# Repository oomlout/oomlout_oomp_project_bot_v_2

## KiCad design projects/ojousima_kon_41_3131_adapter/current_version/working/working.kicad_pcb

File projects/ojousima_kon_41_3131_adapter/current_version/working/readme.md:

# kon_41_3131
 
## summary 
* id: ojousima_kon_41_3131_adapter
* user: ojousima
* name: kon_41_3131
* board: adapter
* repo: https://github.com/ojousima/kon-41.3131
* src_file_repo_kicad_pcb: adapter_board/adapter.kicad_pcb
* src_file_repo_kicad_pcb_link: https://github.com/ojousima/kon-41.3131/tree/master/adapter_board/adapter.kicad_pcb

* src_file_repo_sch: adapter_board/adapter.sch
* src_file_repo_sch_link: https://github.com/ojousima/kon-41.3131/tree/master/adapter_board/adapter.sch
* full details link: https://github.com/oomlout/oomlout_oomp_project_bot_v_2/tree/main/projects/ojousima_kon_41_3131_adapter/current_version/working

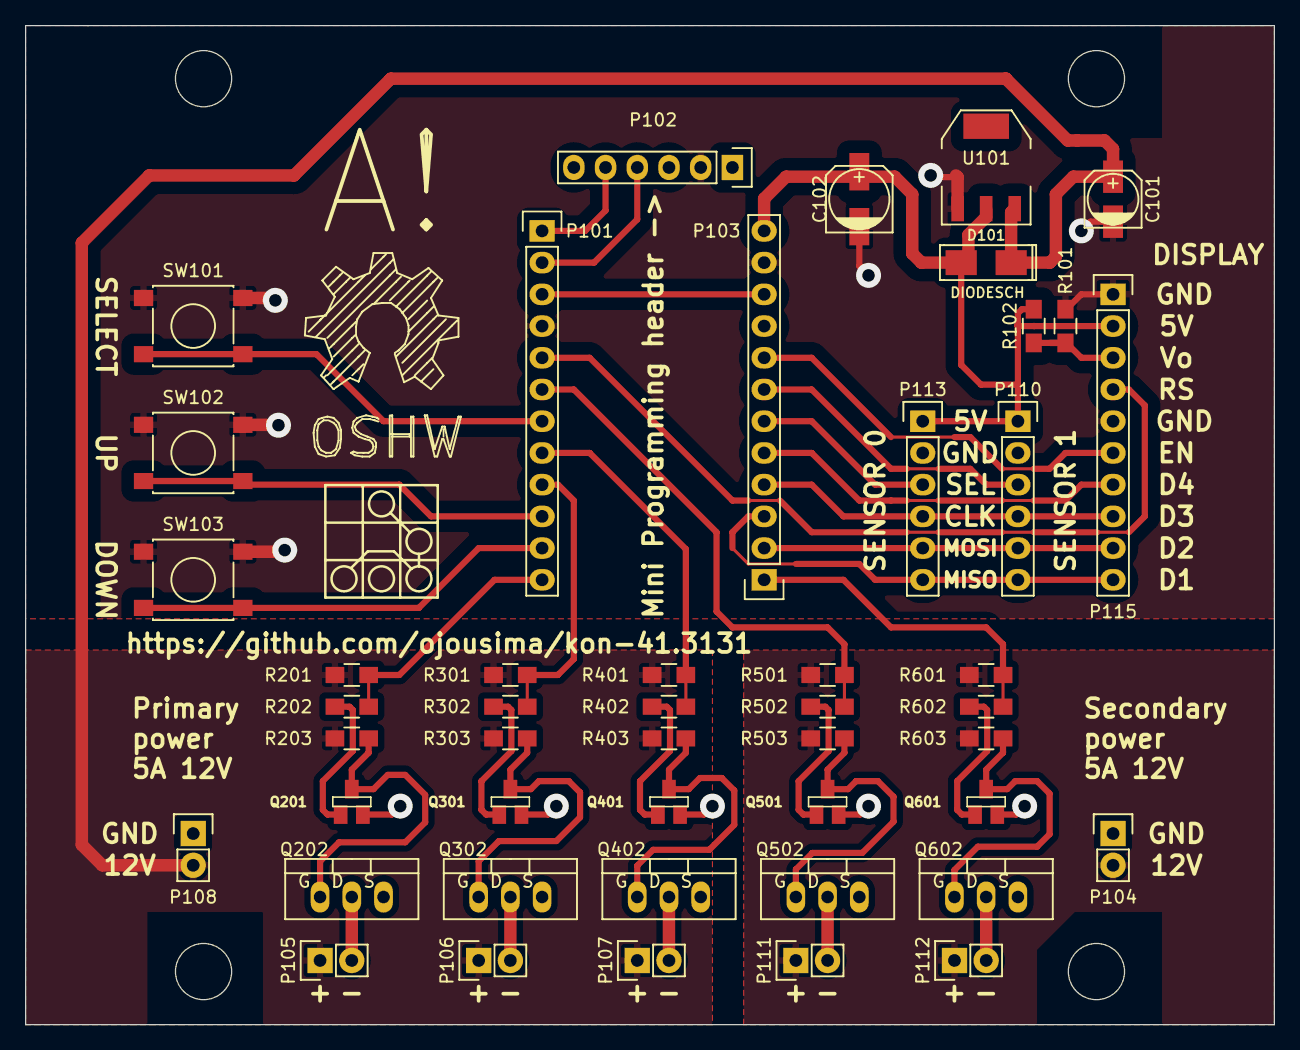
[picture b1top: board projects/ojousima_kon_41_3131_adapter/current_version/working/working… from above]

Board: 2 copper layers, 100.0 x 80.0 mm, 48 parts (0 on the bottom side), 39 nets.

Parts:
C101: 10u; c_elec_4x5.3
C102: 100u; c_elec_5x5.8
D101: DIODESCH; SMA_WAVE
LOGO101: OPEN_HARDWARE_2; Symbol_OSHW-Logo_SilkScreen_BIG
P101, P103: CONN_01X12; Pin_Header_Straight_1x12
P102, P110, P113: CONN_01X06; Pin_Header_Straight_1x06
P104, P105, P106, P107, P108, P111, P112: CONN_01X02; Pin_Header_Straight_1x02
P115: CONN_01X10; Pin_Header_Straight_1x10
Q201, Q301, Q401, Q501, Q601: BC850; SOT23EBC
Q202, Q302, Q402, Q502, Q602: IRF530N; TO-220_FET-GDS_Vertical
R101, R102: R; R_0805_HandSoldering
R201, R203, R301, R303, R401, R403, R501, R503, R601, R603: 10k; R_0805_HandSoldering
R202, R302, R402, R502, R602: 1k; R_0805_HandSoldering
SW101, SW102, SW103: SPST; SW_SPST_PTS645
U101: LD1117S50TR; SOT-223

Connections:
/5V: C102.1, D101.1, P103.12, P110.1, P113.1, P115.2, R101.1, U101.2
/BT0: P101.7, SW101.2
/BT1: P101.10, SW102.2
/BT2: P101.11, SW103.2
/D4: P103.5, P115.7
/MISO: P103.3, P110.6, P113.6, P115.10
/MOSI: P103.2, P110.5, P113.5, P115.9
/PWM0/12V: C101.1, D101.2, P105.1, P106.1, P107.1, P108.2, R201.1, R203.1, R301.1, R303.1, R401.1, R403.1, U101.3
/PWM0/Drain: P105.2, Q202.D
/PWM0/INV_PWM: P101.12, R201.2, R202.2
/PWM1/Drain: P106.2, Q302.D
/PWM1/INV_PWM: P101.9, R301.2, R302.2
/PWM2/Drain: P107.2, Q402.D
/PWM2/INV_PWM: P101.8, R401.2, R402.2
/PWM3/12V: P104.2, P111.1, P112.1, R501.1, R503.1, R601.1, R603.1
/PWM3/Drain: P111.2, Q502.D
/PWM3/INV_PWM: P101.6, R501.2, R502.2
/PWM4/Drain: P112.2, Q602.D
/PWM4/INV_PWM: P103.1, R601.2, R602.2
/RESET: P101.3, P103.10
/RS: P101.5, P115.4
/RXI: P101.2, P102.4
/SCLK: P103.4, P110.4, P113.4, P115.8
/SEL0: P103.6, P113.3
/SEL1: P103.7, P110.3
/SEL2: P103.8, P115.6
/TXO: P101.1, P102.5
/Vo: P115.3, R101.2, R102.1
GND: C101.2, C102.2, P101.4, P102.2, P103.11, P104.1, P108.1, P110.2, P113.2, P115.1, P115.5, Q201.1, Q202.S, Q301.1, Q302.S, Q401.1, Q402.S, Q501.1, Q502.S, Q601.1, Q602.S, R102.2, SW101.1, SW102.1, SW103.1, U101.1
unnamed: Q201.2, R202.1
unnamed: Q201.3, Q202.G, R203.2
unnamed: Q301.2, R302.1
unnamed: Q301.3, Q302.G, R303.2
unnamed: Q401.2, R402.1
unnamed: Q401.3, Q402.G, R403.2
unnamed: Q501.2, R502.1
unnamed: Q501.3, Q502.G, R503.2
unnamed: Q601.2, R602.1
unnamed: Q601.3, Q602.G, R603.2

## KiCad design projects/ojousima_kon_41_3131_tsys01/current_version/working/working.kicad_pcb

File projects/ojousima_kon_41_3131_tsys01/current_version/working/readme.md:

# kon_41_3131
 
## summary 
* id: ojousima_kon_41_3131_tsys01
* user: ojousima
* name: kon_41_3131
* board: tsys01
* repo: https://github.com/ojousima/kon-41.3131
* src_file_repo_kicad_pcb: TSYS01-shield/tsys01.kicad_pcb
* src_file_repo_kicad_pcb_link: https://github.com/ojousima/kon-41.3131/tree/master/TSYS01-shield/tsys01.kicad_pcb
* src_file_repo_kicad_sch: adapter_board/PWM.kicad_sch
* src_file_repo_kicad_sch_link: https://github.com/ojousima/kon-41.3131/tree/master/adapter_board/PWM.kicad_sch

* src_file_repo_sch: TSYS01-shield/tsys01.sch
* src_file_repo_sch_link: https://github.com/ojousima/kon-41.3131/tree/master/TSYS01-shield/tsys01.sch
* full details link: https://github.com/oomlout/oomlout_oomp_project_bot_v_2/tree/main/projects/ojousima_kon_41_3131_tsys01/current_version/working

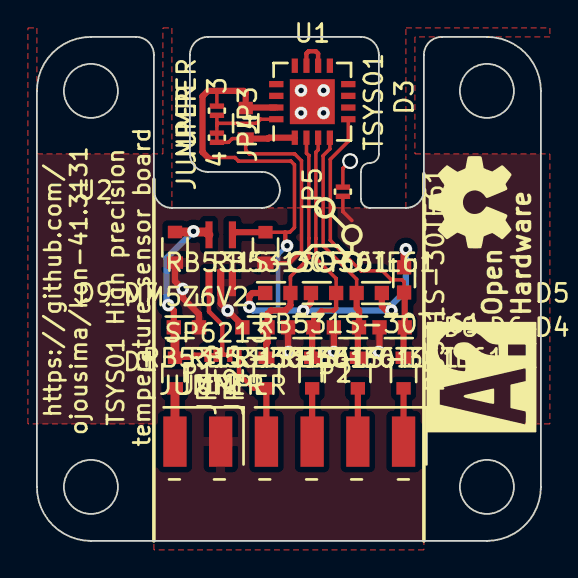
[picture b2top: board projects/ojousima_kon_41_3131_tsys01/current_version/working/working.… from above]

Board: 2 copper layers, 28.0 x 28.0 mm, 26 parts (0 on the bottom side), 14 nets.

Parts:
C1, C2: 2u2; SMD0603_WAVE
C3: 100n; SMD0603_WAVE
D1: MM5Z6V2; SOD-523
D2, D3, D4, D5, D6, D7, D8, D9: RB531S-30TE61; SOD-523
JP1, JP2, JP3, JP4, JP5: JUMPER; R_0201
P1: CONN_01X02; Pin_Header_Angled_SMD_1x02
P2: CONN_01X04; Pin_Header_Angled_SMD_1x04
R1, R2, R3, R4, R5: 220; SMD0603_WAVE
U1: TSYS01; QFN-16-1EP_4x4mm_Pitch0.65mm
U2: SP6213; SC70-6_Handsoldering

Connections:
+3V3: C2.1, C3.1, D3.2, D5.2, D7.2, D9.2, JP3.1, U1.15, U2.4
/CS: JP2.2, P2.4, R2.1
/EN: D8.2, D9.1, R2.2, U1.2
/MISO: P2.1, R5.1
/MOSI: P2.2, R4.1
/PAD: JP5.2, U1.17
/SCLK: P2.3, R3.1
/Vin: C1.1, D1.2, JP1.1, JP1.2, JP2.1, R1.1, U2.1, U2.5
GNDA: C1.2, C2.2, C3.2, D1.1, D2.1, D4.1, D6.1, D8.1, JP3.2, JP4.1, JP4.2, JP5.1, P1.1, U1.1, U1.16, U2.2, U2.3
unnamed: D2.2, D3.1, R5.2, U1.5
unnamed: D4.2, D5.1, R4.2, U1.4
unnamed: D6.2, D7.1, R3.2, U1.3
unnamed: P1.2, R1.2
unnamed: U1.10, U1.11

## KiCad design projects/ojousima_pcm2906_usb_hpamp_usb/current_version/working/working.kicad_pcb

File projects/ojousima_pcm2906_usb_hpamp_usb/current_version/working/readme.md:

# pcm2906_usb_hpamp
 
## summary 
* id: ojousima_pcm2906_usb_hpamp_usb
* user: ojousima
* name: pcm2906_usb_hpamp
* board: usb
* repo: https://github.com/ojousima/PCM2906-usb-hpamp
* src_file_repo_kicad_pcb: usb.kicad_pcb
* src_file_repo_kicad_pcb_link: https://github.com/ojousima/PCM2906-usb-hpamp/tree/master/usb.kicad_pcb

* src_file_repo_sch: usb.sch
* src_file_repo_sch_link: https://github.com/ojousima/PCM2906-usb-hpamp/tree/master/usb.sch
* full details link: https://github.com/oomlout/oomlout_oomp_project_bot_v_2/tree/main/projects/ojousima_pcm2906_usb_hpamp_usb/current_version/working

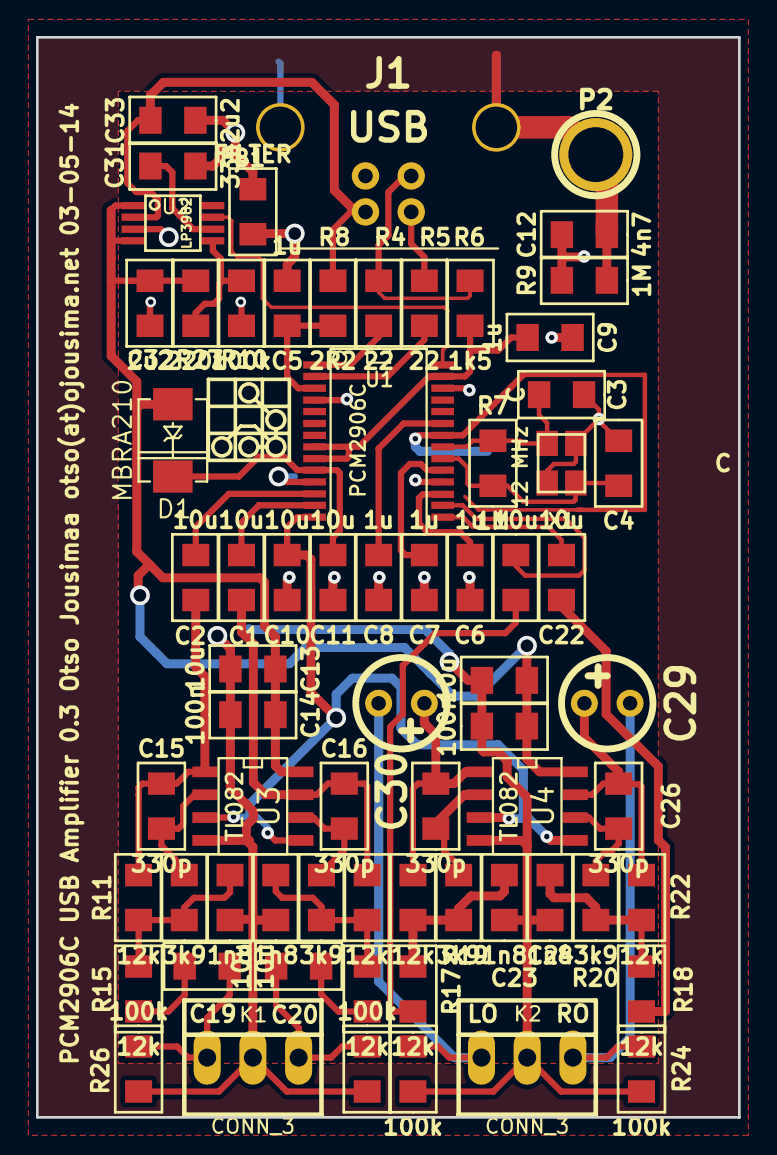
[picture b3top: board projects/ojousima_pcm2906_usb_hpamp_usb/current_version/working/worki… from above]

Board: 2 copper layers, 39.0 x 60.0 mm, 68 parts (0 on the bottom side), 45 nets.

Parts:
C1, C2, C10, C11, C13, C19, C20, C21, C22, C28: 10u; SMD0805_WAVE
C3, C4: C; SMD0805_WAVE
C5, C6, C7, C8, C9: 1u; SMD0805_WAVE
C12: 4n7; SMD0805_WAVE
C14, C27: 100n; SMD0805_WAVE
C15, C16, C25, C26: 330p; SMD0805_WAVE
C17, C18, C23, C24: 1n8; SMD0805_WAVE
C29, C30: 680u; Elko_vert_DM5_RM2-5
C31: 33n; SMD0805_WAVE
C32, C33: 2u2; SMD0805_WAVE
D1: MBRA210; DO-214AA(SMB)
FB1: FILTER; SMD0805_WAVE
J1: USB; USB_B
K1, K2: CONN_3; PINHEAD1-3
P2: CONN_1; 1pin
R4, R5: 22; SMD0805_WAVE
R6: 1k5; SMD0805_WAVE
R7, R9: 1M; SMD0805_WAVE
R8: 2R2; SMD0805_WAVE
R10, R23, R24, R25, R26: 100k; SMD0805_WAVE
R11, R12, R15, R16, R17, R18, R21, R22: 12k; SMD0805_WAVE
R13, R14, R19, R20: 3k9; SMD0805_WAVE
R27: 220k; SMD0805_WAVE
U1: PCM2906C; SSOP-28
U2: LP3982; SSOP-8
U3, U4: TL082; SO8E
X1: 12 MHz; crystal_FA238-TSX3225

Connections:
/ENABLE: U1.28, U2.7
/L_IN: C19.2, K1.1, R26.2
/L_OUT: C30.2, K2.1, R25.1
/R_IN: C20.2, K1.3, R23.2
/R_OUT: C29.2, K2.3, R24.1
/VBUS: C33.1, J1.1, R8.1, U2.2
/VCC: C13.1, C14.1, C27.1, C28.1, C32.1, D1.1, R27.1, U2.1, U2.4, U3.8, U4.8
/VCOM: C10.2, U1.14, U3.3, U3.5, U4.3, U4.5
/Vddi: C9.2, R6.2, U1.8, U1.9, U1.27
AGND: C13.2, C14.2, C17.2, C18.2, C23.2, C24.2, C27.2, C28.2, C31.2, C32.2, C33.2, FB1.2, K1.2, K2.2, R10.2, R23.1, R24.2, R25.2, R26.1, U2.3, U3.4, U4.4
DGND: C3.2, C4.2, C5.2, C6.1, C7.1, C8.1, C9.1, C10.1, C11.1, C12.1, FB1.1, J1.4, R9.1, U1.4, U1.11, U1.18, U1.22, U1.26, X1.3
GND: C12.2, J1.5, J1.6, P2.1, R9.2
unnamed: C1.1, C16.1, R12.1, U3.7
unnamed: C1.2, U1.13
unnamed: C2.2, U1.12
unnamed: C3.1, R7.1, U1.21, X1.1
unnamed: C4.1, R7.2, U1.20, X1.2
unnamed: C5.1, R8.2, U1.3
unnamed: C6.2, U1.17
unnamed: C7.2, U1.19
unnamed: C8.2, U1.23
unnamed: C11.2, D1.2, U1.10
unnamed: C2.1, C15.1, R11.1, U3.1
unnamed: C15.2, R13.1, U3.2
unnamed: C16.2, R14.1, U3.6
unnamed: C17.1, R11.2, R13.2, R15.1
unnamed: C18.1, R12.2, R14.2, R16.1
unnamed: C19.1, R15.2
unnamed: C20.1, R16.2
unnamed: C21.1, R17.2
unnamed: C21.2, U1.16
unnamed: C22.1, R18.2
unnamed: C22.2, U1.15
unnamed: C23.1, R17.1, R19.2, R21.2
unnamed: C24.1, R18.1, R20.2, R22.2
unnamed: C25.1, C30.1, R21.1, U4.1
unnamed: C25.2, R19.1, U4.2
unnamed: C26.1, C29.1, R22.1, U4.7
unnamed: C26.2, R20.1, U4.6
unnamed: C31.1, U2.6
unnamed: J1.2, R5.1
unnamed: J1.3, R4.1, R6.1
unnamed: R4.2, U1.1
unnamed: R5.2, U1.2
unnamed: R10.1, R27.2, U2.5

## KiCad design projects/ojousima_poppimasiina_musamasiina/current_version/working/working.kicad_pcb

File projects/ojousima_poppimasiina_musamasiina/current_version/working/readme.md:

# poppimasiina
 
## summary 
* id: ojousima_poppimasiina_musamasiina
* user: ojousima
* name: poppimasiina
* board: musamasiina
* repo: https://github.com/ojousima/poppimASiina
* src_file_repo_kicad_pcb: hardware/musamasiina.kicad_pcb
* src_file_repo_kicad_pcb_link: https://github.com/ojousima/poppimASiina/tree/master/hardware/musamasiina.kicad_pcb

* src_file_repo_sch: 
* src_file_repo_sch_link: https://github.com/ojousima/poppimASiina/tree/master/
* full details link: https://github.com/oomlout/oomlout_oomp_project_bot_v_2/tree/main/projects/ojousima_poppimasiina_musamasiina/current_version/working

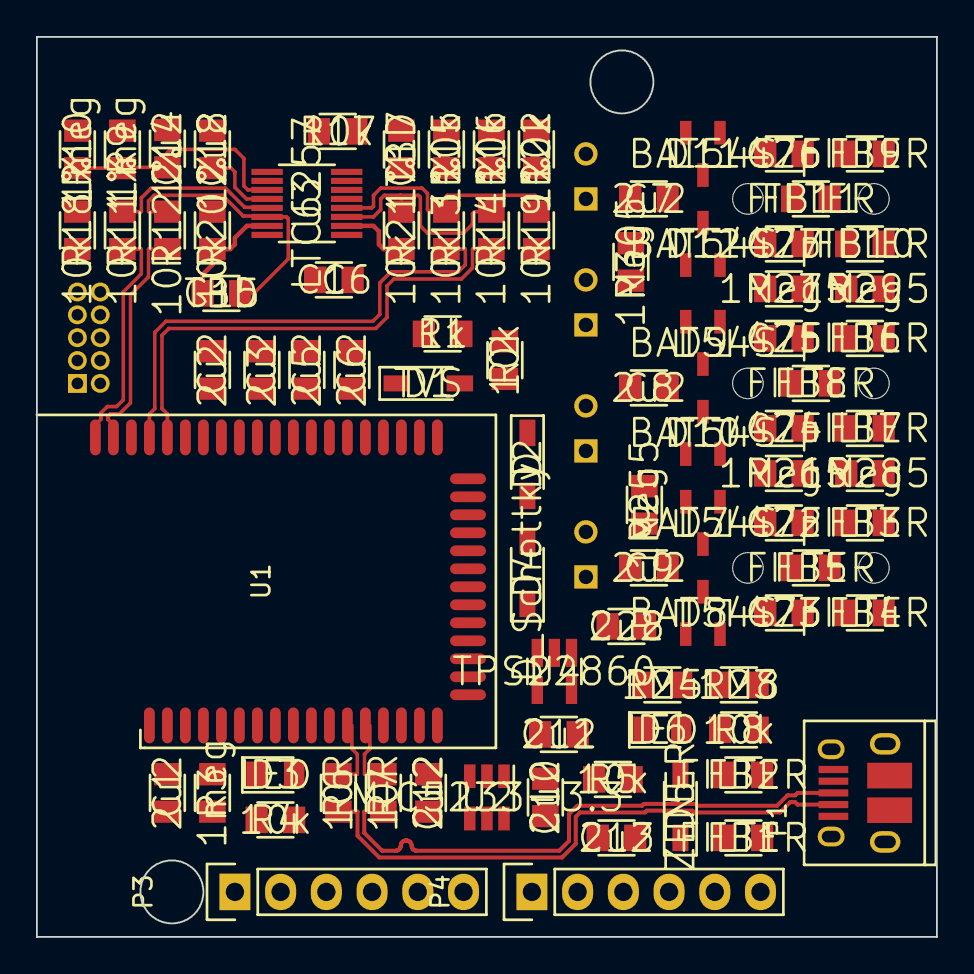
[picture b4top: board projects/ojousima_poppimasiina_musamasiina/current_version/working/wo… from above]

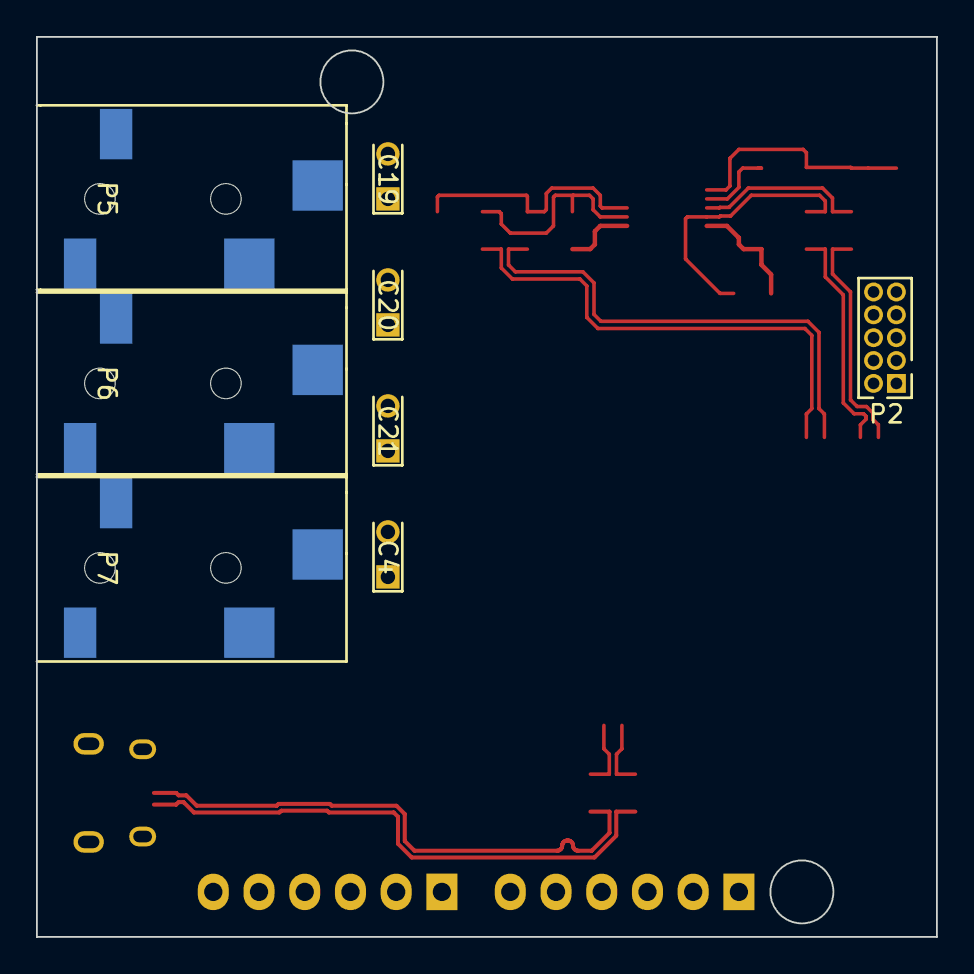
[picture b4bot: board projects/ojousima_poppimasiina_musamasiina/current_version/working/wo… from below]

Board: 2 copper layers, 50.0 x 50.0 mm, 92 parts (8 on the bottom side), 68 nets.

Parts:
C1, C2, C3, C5, C6, C7, C8, C9, C10, C11, C12, C13, C14, C18, C28: 2u2; SMD0805-CAP-M
C4: AFK477M10F24T-F; C_Radial_D6.3_L13_P2-5_Bent
C15, C17: TBD; SMD0805-CAP-M
C16: C; SMD0805-CAP-M
C19, C20, C21: 470u; C_Radial_D6.3_L13_P2-5_Bent
C22, C23, C24, C25, C26, C27: 47p; SMD0805-CAP-M
D1: TVS; SOD323-M
D2: D; SOD323-M
D3, D6: LED; SMD0805-LED-M
D4: D_Schottky; SOD323-M
D5: ZENER; SOD323-M
D7, D8, D9, D10, D11, D12: BAT54S; SOT23-M
FB1, FB2, FB3, FB4, FB5, FB6, FB7, FB8, FB9, FB10, FB11: FILTER; SMD0805-FERRITE-M
P1: USB_OTG; USB_Micro-B_10103594-0001LF
P2: CONN_02X05; Pin_Header_Straight_2x05_Pitch1.27mm
P3: CONN_02X03; Pin_Header_Straight_1x06
P4: CONN_01X06; Pin_Header_Straight_1x06
P5, P6, P7: CONN_01X03; SMD_3-5mm_jack_CUI-SJ-352X-SMT
R1: 1k; SMD0805-RES-M
R2, R4, R5, R8, R15, R16, R17, R22: 10k; SMD0805-RES-M
R3, R9, R10: 1meg; SMD0805-RES-M
R6, R7: 10R; SMD0805-RES-M
R11, R12, R13, R14, R18, R19, R20, R21: 10k 1%; SMD0805-RES-M
R23: 1M8; SMD0805-RES-M
R24: 1M5; SMD0805-RES-M
R25, R26, R27, R28, R29, R30: 1Meg5; SMD0805-RES-M
U1: WT32
U2: MIC5233-3.3; SOT23-6-M
U3: LTC6257; MSOP16-05mm-M
U4: TPS22860; SOT23-5-M

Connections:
+5V: C10.1, C13.1, D4.1, D5.1, FB1.2, R8.1, U2.1
+BATT: C4.1, C11.1, D1.1, D4.2, U1.37, U4.4, U4.5
/Analog/LEFT_OPAMP+: R11.1, R18.1, U3.5
/Analog/LEFT_OPAMP-: C15.2, R12.1, R20.2, U3.6
/Analog/LEFT_SE: C15.1, C19.2, R15.2, R20.1, U3.7
/Analog/LO_N: R12.2, U1.49
/Analog/LO_P: R11.2, U1.50
/Analog/RIGHT_OPAMP+: R13.1, R19.1, U3.12
/Analog/RIGHT_OPAMP-: C16.2, R14.1, R21.2, U3.11
/Analog/RIGHT_SE: C16.1, C20.2, R16.2, R21.1, U3.10
/Analog/RO_N: R14.2, U1.46
/Analog/RO_P: R13.2, U1.47
/CD+: R7.1, U1.12
/CD-: R6.1, U1.11
/IN_LEFT: C5.2, U1.44
/IN_RIGHT: C6.2, U1.41
/Line in/ESD+: C9.1, D7.2, D8.2, R23.2, R24.1
/Line in/GROUND_CABLE: FB5.2, P7.2
/Line in/LEFT_CABLE: FB3.2, P7.1
/Line in/LEFT_DEVICE: C5.1, C22.1, D7.3, FB3.1, R26.1
/Line in/RIGHT_CABLE: FB4.2, P7.3
/Line in/RIGHT_DEVICE: C6.1, C23.1, D8.3, FB4.1, R25.1
/MISO: P3.1, U1.34
/MOSI: P3.4, U1.35
/MUTE: P2.7, U1.14
/Mono out/GROUND_CABLE: FB8.2, P6.2
/Mono out/LEFT_CABLE: FB6.2, P6.1
/Mono out/LEFT_DEVICE: C21.1, C24.1, C25.1, D9.3, D10.3, FB6.1, FB7.1, R27.1, R28.1
/Mono out/RIGHT_CABLE: FB7.2, P6.3
/NEXT: P2.4, U1.24
/PAUSE: P2.6, U1.22
/PLAY: P2.8, U1.13
/PREV: P2.2, U1.25
/Power Supply/CHRG: D6.1, U1.36
/Power Supply/ENABLE: D2.1, R2.2, U2.3
/Power Supply/GNDBUS: FB2.1, P1.4, P1.5
/Power Supply/VBUS: FB1.1, P1.1
/RESET: P3.5, U1.19
/RXD: P4.4, R5.1, U1.15
/SCLK: P3.3, U1.33
/STOP: P2.9, U1.23
/Stereo out/GROUND_CABLE: FB11.2, P5.2
/Stereo out/LEFT_CABLE: FB9.2, P5.1
/Stereo out/LEFT_DEVICE: C19.1, C26.1, D11.3, FB9.1, R30.1
/Stereo out/RIGHT_CABLE: FB10.2, P5.3
/Stereo out/RIGHT_DEVICE: C20.1, C27.1, D12.3, FB10.1, R29.1
/TXD: P4.5, U1.16
/USB_D+: P1.3, R7.2
/USB_D-: P1.2, R6.2
/VOL+: P2.5, U1.26
/VOL-: P2.3, U1.10
GNDA: C2.1, C3.1, C7.2, C8.2, C9.2, C14.2, C18.1, C22.2, C23.2, C24.2, C25.2, C26.2, C27.2, C28.2, D7.1, D8.1, D9.1, D10.1, D11.1, D12.1, FB5.1, FB8.1, FB11.1, R10.2, R25.2, R26.2, R27.2, R28.2, R29.2, R30.2, U1.39, U1.43, U1.48, U3.13, U4.2
GNDD: C1.2, C4.2, C10.2, C11.2, C12.2, C13.2, D5.2, FB2.2, P2.10, P3.6, P4.1, R3.2, R4.2, R24.2, U1.2, U1.3, U1.4, U1.18, U1.31, U2.2
unnamed: C1.1, D2.2, R1.1, U1.1
unnamed: C2.2, U1.45
unnamed: C3.2, U1.42
unnamed: C14.1, R9.2, R10.1, U3.3
unnamed: C17.1, C21.2, R22.1, U3.16
unnamed: C17.2, R17.1, R22.2, U3.15
unnamed: D1.2, R1.2
unnamed: D3.1, R4.1
unnamed: D3.2, R2.1, R3.1, U1.7
unnamed: D6.2, R8.2
unnamed: R15.1, R16.1, U3.14
unnamed: U1.20, U1.21
VAA: C7.1, C8.1, C18.2, C28.1, D9.2, D10.2, D11.2, D12.2, R9.1, U3.4, U4.1
VCOM: R17.2, R18.2, R19.2, U3.1, U3.2
VDD: C12.1, P2.1, P3.2, P4.3, R5.2, R23.1, U1.17, U2.5

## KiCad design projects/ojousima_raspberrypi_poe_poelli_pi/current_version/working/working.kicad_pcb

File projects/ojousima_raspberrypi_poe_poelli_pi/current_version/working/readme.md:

# raspberrypi_poe
 
## summary 
* id: ojousima_raspberrypi_poe_poelli_pi
* user: ojousima
* name: raspberrypi_poe
* board: poelli_pi
* repo: https://github.com/ojousima/RaspberryPi-PoE
* src_file_repo_kicad_pcb: PoELLi_PI.kicad_pcb
* src_file_repo_kicad_pcb_link: https://github.com/ojousima/RaspberryPi-PoE/tree/master/PoELLi_PI.kicad_pcb

* src_file_repo_sch: PoELLi_PI.sch
* src_file_repo_sch_link: https://github.com/ojousima/RaspberryPi-PoE/tree/master/PoELLi_PI.sch
* full details link: https://github.com/oomlout/oomlout_oomp_project_bot_v_2/tree/main/projects/ojousima_raspberrypi_poe_poelli_pi/current_version/working

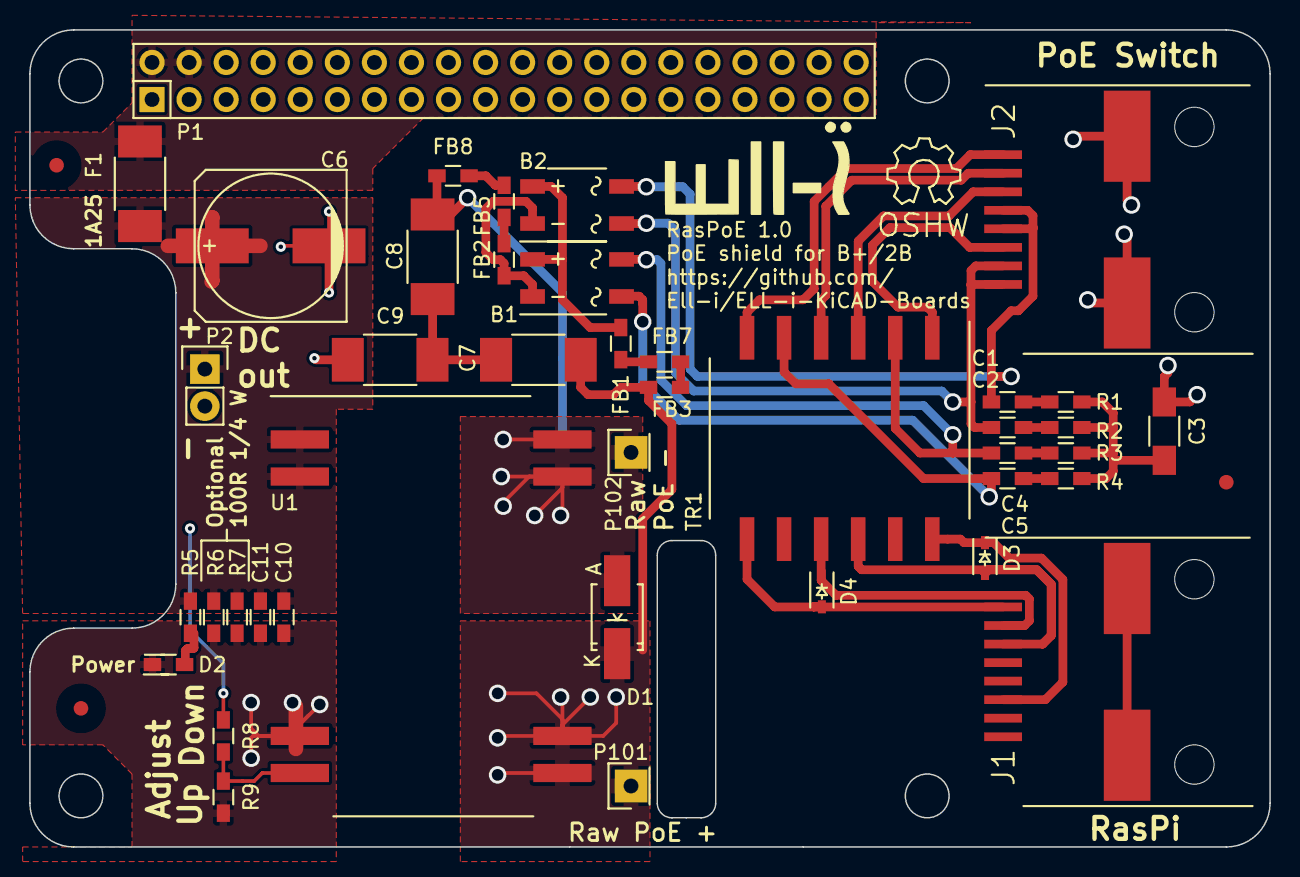
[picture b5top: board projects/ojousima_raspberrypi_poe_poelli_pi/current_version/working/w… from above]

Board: 2 copper layers, 85.0 x 56.0 mm, 46 parts (0 on the bottom side), 32 nets.

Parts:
B1, B2: MB110S; TO-269AA
C1, C2, C4, C5: 10n 100V; R_0603_HandSoldering
C3: 1n 2kV; C_1206_HandSoldering
C6: 470u; c_elec_10x10
C7, C8, C9: 4n7 2kV; C_1812_HandSoldering
C10: 10n; R_0603_HandSoldering
C11: 10u; R_0603_HandSoldering
D1: SMA58; Diode-SMA_Handsoldering
D2: LED; R_0603_HandSoldering
D3, D4: TVS; SOD-323
F1: FUSE; C_1812_HandSoldering
FB1, FB2, FB3, FB5, FB7, FB8: FILTER; R_0603_HandSoldering
FID1, FID2, FID3: 1, 2 mm; Fiducial_2mm_dia
J1: RJSSE-5080; RJSSE-5380
J2: RJSSE-5380
LOGO101: OPEN_HARDWARE_1; Symbol_OSHW-Logo_SilkScreen
LOGO102: ELL-i; ELL-i_large
P1: CONN_02X20; Pin_Header_Straight_2x20
P2: CONN_01X02; Pin_Header_Straight_1x02
P101, P102: CONN_01X01; Pin_Header_Straight_1x01
R1, R2, R3, R4: 75R; R_0603_HandSoldering
R5: 180R; R_0603_HandSoldering
R6, R7: 100R 250 mW; R_0603_HandSoldering
R8, R9: R; R_0603_HandSoldering
TR1: 749012011; WE_749012011
U1: AG9800

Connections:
+5V: F1.2, P1.2, P1.4
/ADJ: R8.2, R9.1, U1.4
/AG_IN_+: C7.1, D1.2, FB7.2, P101.1, U1.5, U1.6
/AG_IN_-: C8.1, D1.1, FB8.2, P102.1, U1.7, U1.8
/AG_OUT_+: C6.1, C10.1, C11.1, F1.1, P2.1, R5.1, R6.1, R7.1, U1.1, U1.2
/POE_A+: B1.2, C5.1, TR1.5
/POE_A-: B1.4, C4.1, TR1.2
/POE_B+: B2.2, C2.1, J2.7, J2.8
/POE_B-: B2.4, C1.1, J2.4, J2.5
/RD+: D3.2, J1.3, TR1.10
/RD-: D3.1, J1.6, TR1.12
/RX+: J2.3, TR1.3
/RX-: J2.6, TR1.1
/TD+: D4.2, J1.1, TR1.7
/TD-: D4.1, J1.2, TR1.9
/TX+: J2.1, TR1.6
/TX-: J2.2, TR1.4
/VIN: B1.3, B2.3, FB1.1
GND: C6.2, C9.1, C10.2, C11.2, D2.2, P1.6, P1.9, P1.14, P1.20, P1.25, P1.30, P1.34, P1.39, P2.2, R6.2, R7.2, R9.2, U1.3
GNDA: C3.2, J2.9
GNDD: B1.1, B2.1, FB2.1
unnamed: C1.2, R1.1
unnamed: C2.2, R2.1
unnamed: C3.1, R1.2, R2.2, R3.2, R4.2
unnamed: C4.2, R3.1
unnamed: C5.2, R4.1
unnamed: C7.2, C8.2, C9.2
unnamed: D2.1, R5.2
unnamed: FB1.2, FB3.1
unnamed: FB2.2, FB5.1
unnamed: FB3.2, FB7.1
unnamed: FB5.2, FB8.1

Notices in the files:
projects/ojousima_ruuvitag_hw_ruuvitag_reva1/current_version/working/working.kicad_sch:
http://creativecommons.org/licenses/by-sa/4.0
License: Attribution-ShareAlike 4.0 International (CC BY-SA 4.0)
